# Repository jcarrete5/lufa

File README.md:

# Rock Band 3 MIDI Adapter
Adapts a MIDI input to a RB3 drum kit.

## Build Dependencies
- [Mako](https://www.makotemplates.org/download.html) - a python templating solution

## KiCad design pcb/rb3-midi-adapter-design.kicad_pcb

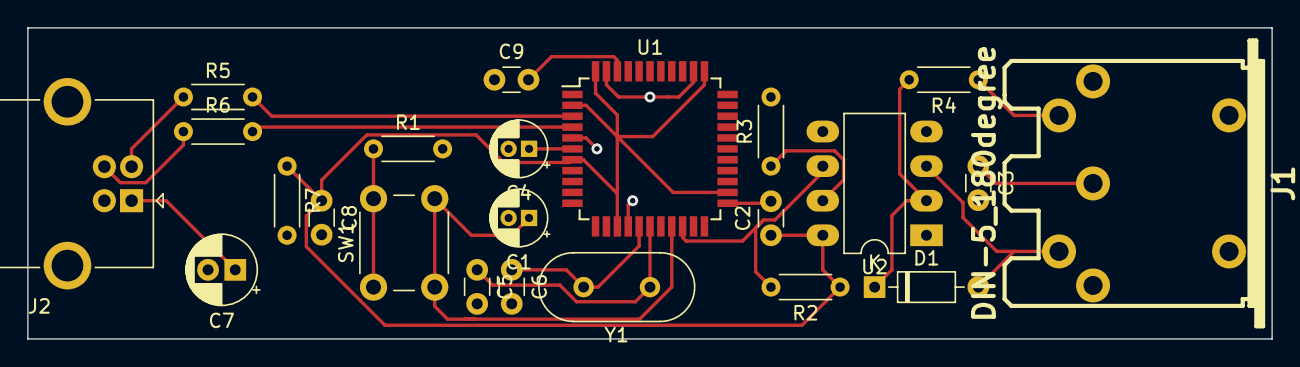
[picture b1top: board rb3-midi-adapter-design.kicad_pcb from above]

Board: 2 copper layers, 91.4 x 22.9 mm, 23 parts (0 on the bottom side), 19 nets.

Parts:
C1, C4: 1u; CP_Radial_D4.0mm_P1.50mm
C2, C3, C8, C9: 100n; C_Disc_D3.0mm_W1.6mm_P2.50mm
C5, C6: 22p; C_Disc_D3.0mm_W1.6mm_P2.50mm
C7: 22u; CP_Radial_D5.0mm_P2.00mm
D1: 1N4148; D_DO-35_SOD27_P7.62mm_Horizontal
J1: DIN-5_180degree; MIDI_DIN5
J2: USB_B; USB_B_OST_USB-B1HSxx_Horizontal
R1, R2: 1k; R_Axial_DIN0204_L3.6mm_D1.6mm_P5.08mm_Horizontal
R3, R7: 10k; R_Axial_DIN0204_L3.6mm_D1.6mm_P5.08mm_Horizontal
R4: 220; R_Axial_DIN0204_L3.6mm_D1.6mm_P5.08mm_Horizontal
R5, R6: 22; R_Axial_DIN0204_L3.6mm_D1.6mm_P5.08mm_Horizontal
SW1: SW_Push; SW_PUSH_6mm_H8mm
U1: ATmega32U4-MU; TQFP-44_10x10mm_P0.8mm
U2: 6N138; DIP-8_W7.62mm_LongPads
Y1: 16MHz; Crystal_HC49-4H_Vertical

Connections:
+5V: C2.1, C8.1, R2.1, R7.1, U1.2, U1.7, U1.14, U1.24, U1.34, U1.44, U2.8
/RX: R2.2, U1.20, U2.6
/START_BTN: C1.1, SW1.2, U1.19
GND: C1.2, C2.2, C3.2, C4.2, C5.2, C6.2, C7.2, C8.2, C9.1, J2.4, J2.5, R1.2, R3.2, R7.2, U1.5, U1.15, U1.23, U1.35, U1.43, U2.5
unnamed: C3.1, J1.2
unnamed: C4.1, U1.6
unnamed: C5.1, U1.17, Y1.1
unnamed: C6.1, U1.16, Y1.2
unnamed: C7.1, J2.1
unnamed: C9.2, U1.42
unnamed: D1.1, R4.2, U2.2
unnamed: D1.2, J1.5, U2.3
unnamed: J1.4, R4.1
unnamed: J2.2, R5.1
unnamed: J2.3, R6.1
unnamed: R1.1, SW1.1
unnamed: R3.1, U2.7
unnamed: R5.2, U1.3
unnamed: R6.2, U1.4

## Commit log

2021-10-21 Parse MIDI "Note On" messages
2021-10-23 Track state as MIDI notes are received
2021-11-06 Connect to PS3 with HID
    The adapter "works" but not very well. Notes can often not register for
    unknown reasons.
2021-11-06 Start work on adapter schematics and PCB
2022-05-04 Update KiCad project files to latest version
2022-05-04 Rename rb3-midi-adapter-design -> kicad
2022-05-04 Add .idea project files
2022-05-04 Ignore all build output
2022-05-04 Move source files into src/ directory
2022-05-09 Rename kicad/ -> pcb/
2022-05-09 Set bcdDevice to version 2.0
    The normal RB3 adapter uses this version so I should probably use it too
    to avoid the PS3 possibly choosing an incorrect driver for the adapter
2022-05-11 Cleanup rb3-midi-adapter.c/h
2022-05-11 Add avrdude-read-ee target to read eeprom from MCU
2022-05-18 Remove unused includes from rb3-midi-adapter.c
2022-07-12 Generate PadConfig.c from json configuration
2022-07-12 Fix include in MIDI.c
2022-07-12 Use -O3
2022-07-14 Use mako to generate PadConfig.h
2022-07-17 Cleanup PadConfig.h.mako a bit
2022-09-11 Remove boilerplate header info
2022-09-11 Remove python3 facet
2022-09-11 Add PadConfig.json dependency to PadConfig.h
2022-09-11 Use circular buffer instead of linked list for buffering midi bytes
    This appears to have increased performance compared to the linked list.
2023-01-31 Use circular buffer instead of linked list for HID report buffer
    This appears to have increased performance compared to the linked list.
2023-01-31 Update compiler flags
2023-01-31 Add extra comments to MIDI buffer
2023-01-31 Minor formatting and type fixes
2023-01-31 Update schematic
2024-05-17 Migrate kicad to 8.0
2024-06-26 Run clang-format on source code
2024-07-02 Adjust code style
2024-07-02 Use "gnu2x" C standard and adjust warnings
2024-07-02 Update kicad_pro
2024-07-02 Create separate function for atomically enqueuing midi bytes
2024-07-02 Declare midi buffer data and count volatile
    These fields may be accessed from both inside and outside an ISR and
    should be declared volatile to prevent the compiler from optimizing away
    accesses to that data.
2024-07-02 Remove unused IDE project metadata
2024-07-08 Adjust app config values
    Made the MIDI_TTL more in line with what is seen on the actual
    controller and reducing the max number of midi bytes processed at once
2024-07-08 Increase optimization level
2024-07-08 Fix includes and warnings in HIDReport.c
2024-07-08 Remove prev hid_report
    This avoids wasting time comparing HID reports. Instead, HID reports are
    always sent regardless if they are the exact same. Sometimes they will
    be the same and that's okay. The original rb3 drum kit does this too.
2024-07-12 Update .clang-format
2024-07-15 Create CMakeLists.txt files
2024-07-15 Initial CMake files
